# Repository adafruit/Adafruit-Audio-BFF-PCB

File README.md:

## Adafruit Audio BFF Add-on for QT Py and Xiao PCB

<a href="http://www.adafruit.com/products/5769"><br/>
Click here to purchase one from the Adafruit shop</a>

PCB files for the Adafruit Audio BFF Add-on for QT Py and Xiao. 

Format is EagleCAD schematic and board layout
* https://www.adafruit.com/product/5769

### Description

Our QT Py boards are a great way to make very small microcontroller projects that pack a ton of power - and now we have a way for you to turn many QT Py boards into powerful audio play projects that are super small!

This BFF comes with a MicroSD card slot that can address up to 64 GB of storage and a I2S 3 Watt amplifier, for high-quality audio playback, that can fit on the back of your miniature dev board. All together uses the SPI port plus 4 GPIO pins for card CS, and I2S data, clock and left-right select.

We call this the Adafruit Audio BFF - a "Best Friend Forever". When you were a kid, you may have learned about the "buddy" system; well, this product is kinda like that! A board that will watch your QT Py's back and give it more capabilities.

This PCB is designed to fit onto the back of any QT Py or Xiao board, it can be soldered into place or use pin and socket headers to make it removable. Onboard is a MAX98357 audio amplifier and picoblade-compatible connector for plugging in a 4 or 8 ohm speaker. We use A1 for the audio data, A2 for wordselect clock, and A3 for bitclock. The SD card connects over the SPI port: MOSI, MISO and SCK plus A0 for card select.

This pinout will work with ESP32 series, nRF52840, and RP2040 chipset boards. It won't work with the ATSAMD21 'original 'QT Py because those pins on the SAMD21 are not I2S capable. However, you could cut and rewire the traces to connect to the I2S pads if desired - personally, we recommend just upgrading to an RP2040 QT Py instead.

We include some header that you can solder to your QT Py. You can also pick up an Itsy Bitsy short female header kit to make it removable but compact, you'll just need to trim down the headers to 7 pins long.

* Comes as an assembled and tested PCB
* For any QT Py or Xiao boards
* Contains a MAX98357 3 Watt audio amplifier pre-configured for 'stereo' mix output and 9 dB gain which will work great for any project.
* Use any micro SD card that supports SPI mode with one CS pin.
* Connect to the speaker output with a picoblade-compatible 2-pin cable. We recommend this 3W 4 ohm speaker
* There are various Arduino / CircuitPython / MicroPython libraries can be used to talk to the SD card and I2S amplifier.

Speaker, microSD memory card, and QT Py are not included.

### License

Adafruit invests time and resources providing this open source design, please support Adafruit and open-source hardware by purchasing products from [Adafruit](https://www.adafruit.com)!

Designed by Limor Fried/Ladyada for Adafruit Industries.

Creative Commons Attribution/Share-Alike, all text above must be included in any redistribution. 
See license.txt for additional details.

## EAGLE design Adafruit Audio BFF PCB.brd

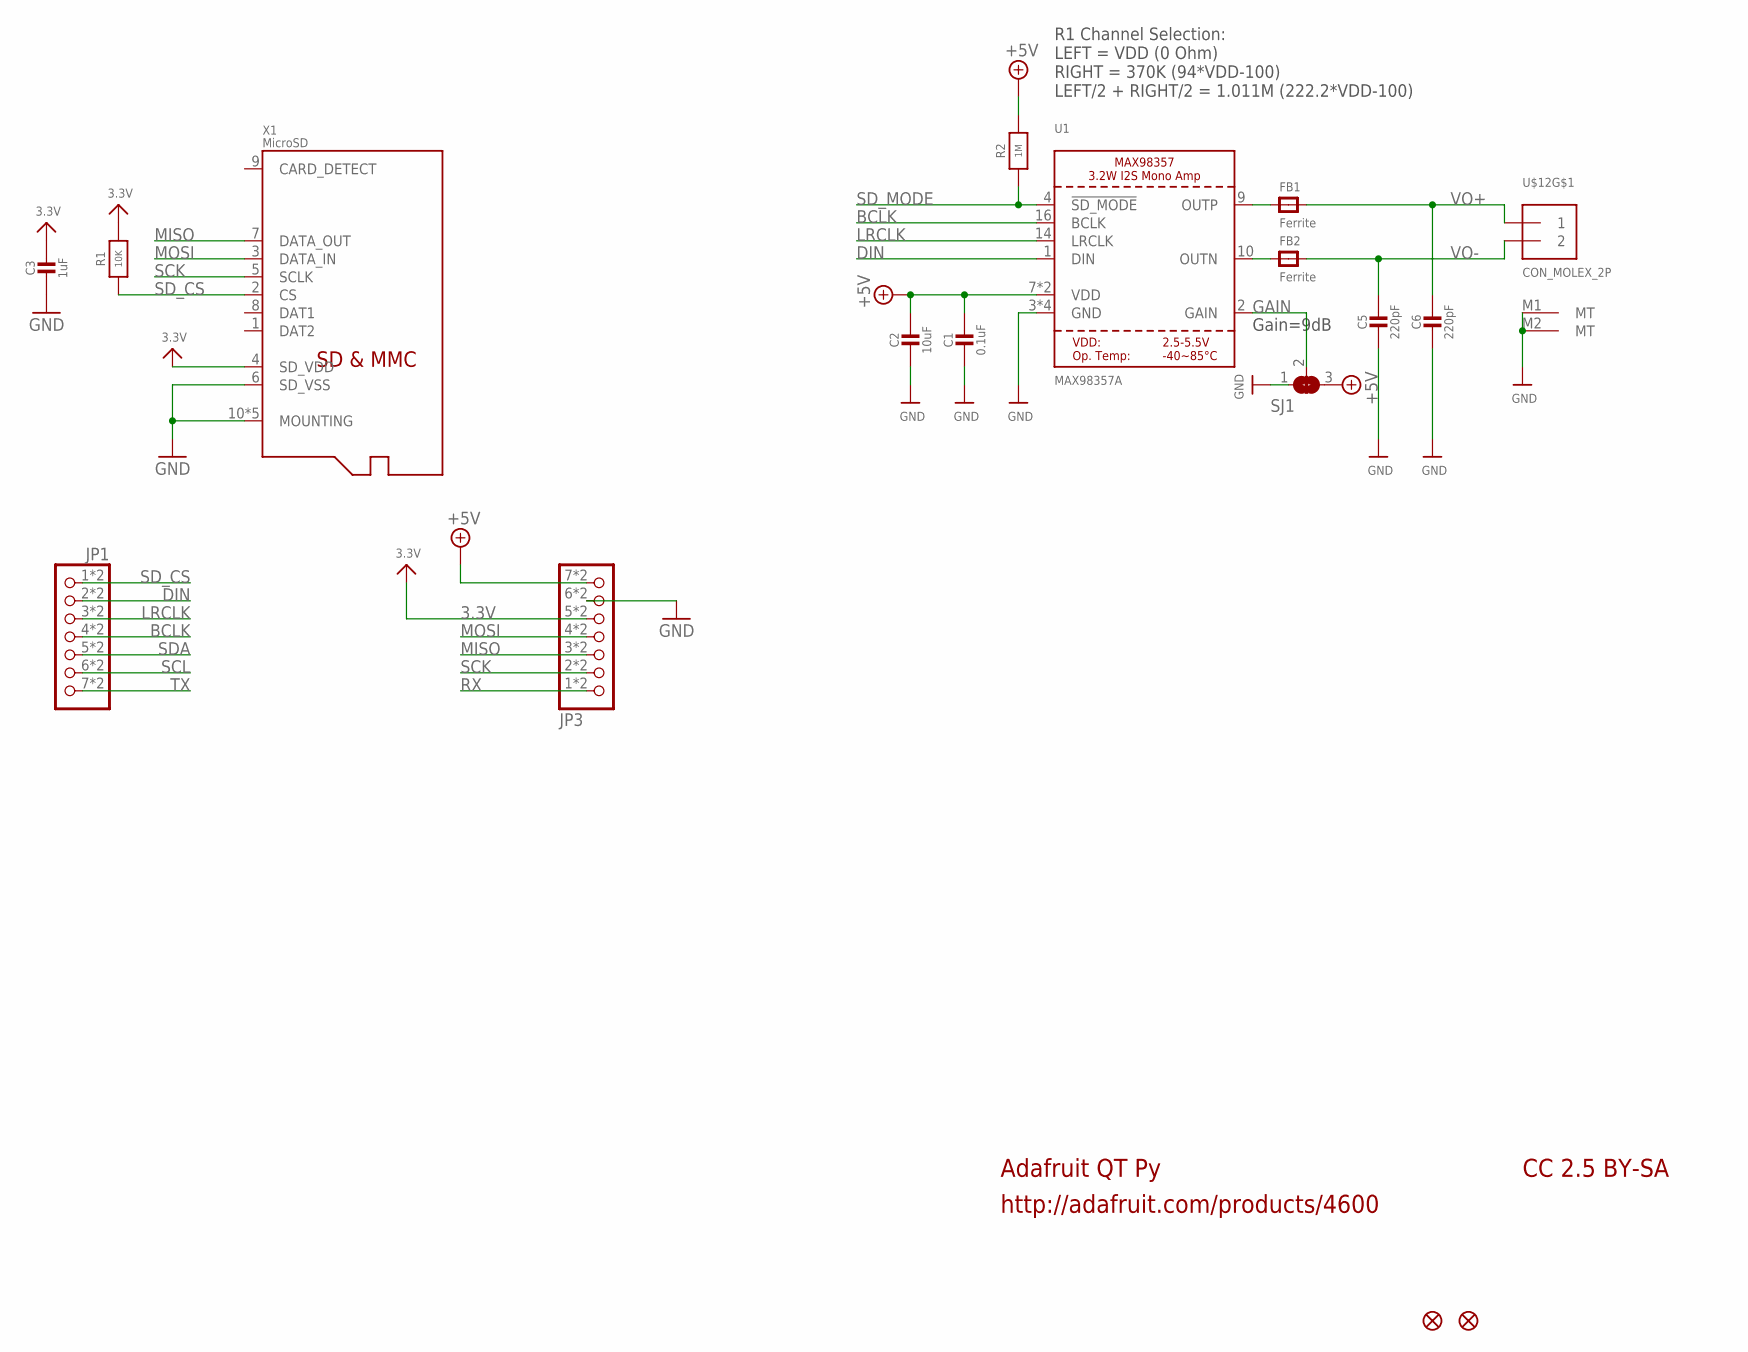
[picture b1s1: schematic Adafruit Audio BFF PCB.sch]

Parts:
C1: 0.1uF; _0402NO
C2: 10uF; 0805-NO
C3: 1uF; _0402NO
C5, C6: 220pF; _0402NO
FB1, FB2: Ferrite; _0402
JP1, JP3: HEADER-1X7_CASTEL; 1X07_CASTEL
R1: 10K; _0402NO
R2: 1M; _0402NO
SJ1: SOLDERJUMPER_2WAY; SOLDERJUMPER_2WAY_OPEN_NOPASTE
U1: MAX98357A; QFN16_3MM
U$6, U$8: FIDUCIAL_1MM
U$12: CON_MOLEX_2P; 53398-0271
X1: MicroSD; MOLEX_104031-0811

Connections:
3.3V: C3.1, JP3.5, JP3.5C (5), R1.2, X1.4 (SD_VDD)
+5V: C1.1, C2.1, JP3.7, JP3.7C (7), R2.2, SJ1.3, U1.7 (VDD), U1.8 (VDD)
BCLK: JP1.4, JP1.4C (4), U1.16 (BCLK)
DIN: JP1.2, JP1.2C (2), U1.1 (DIN)
GAIN: SJ1.2, U1.2 (GAIN)
GND: C1.2, C2.2, C3.2, C5.2, C6.2, JP3.6, JP3.6C (6), SJ1.1, U1.3 (GND), U1.11 (GND), U1.15 (GND), U1.THERMAL (GND), U$12.M1 (MT), U$12.M2 (MT), X1.6 (SD_VSS), X1.10 (MOUNTING), X1.G1 (MOUNTING), X1.G2 (MOUNTING), X1.G3 (MOUNTING), X1.G4 (MOUNTING)
LRCLK: JP1.3, JP1.3C (3), U1.14 (LRCLK)
MISO: JP3.3, JP3.3C (3), X1.7 (DATA_OUT)
MOSI: JP3.4, JP3.4C (4), X1.3 (DATA_IN)
unnamed: FB2.1, U1.10 (OUTN)
unnamed: FB1.1, U1.9 (OUTP)
RX: JP3.1, JP3.1C (1)
SCK: JP3.2, JP3.2C (2), X1.5 (SCLK)
SCL: JP1.6, JP1.6C (6)
SDA: JP1.5, JP1.5C (5)
SD_CS: JP1.1, JP1.1C (1), R1.1, X1.2 (CS)
SD_MODE: R2.1, U1.4 (!SD_MODE)
TX: JP1.7, JP1.7C (7)
VO+: C6.1, FB1.2, U$12.1
VO-: C5.1, FB2.2, U$12.2

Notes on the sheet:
Adafruit QT Py
http://adafruit.com/products/4600
CC 2.5 BY-SA
R1 Channel Selection: LEFT = VDD (0 Ohm) RIGHT = 370K (94*VDD-100) LEFT/2 + RIGHT/2 = 1.011M (222.2*VDD-100)
Gain=9dB

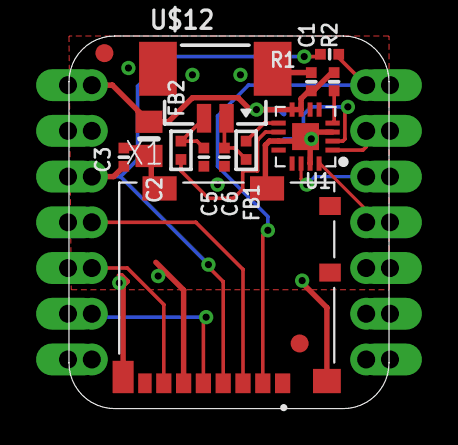
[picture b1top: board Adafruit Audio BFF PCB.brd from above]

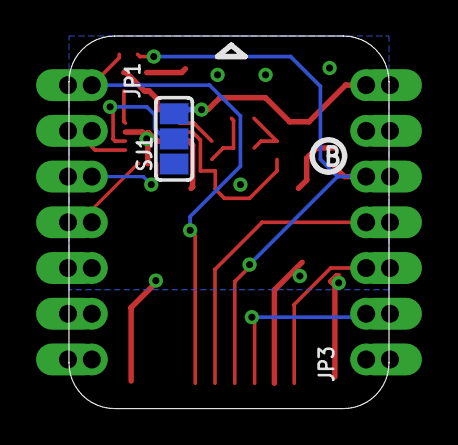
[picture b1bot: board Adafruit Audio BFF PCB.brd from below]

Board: 2 copper layers, 17.8 x 20.7 mm, 30 parts (11 on the bottom side), 20 nets.

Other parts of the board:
PLABEL6: PLABEL6
PLABEL7: PLABEL7
PLABEL8: PLABEL8
PLABEL9: PLABEL9
PLABEL10: PLABEL10
PLABEL11: PLABEL11
PLABEL12: PLABEL12
PLABEL13: PLABEL13
PLABEL14: PLABEL14
PLABEL15: PLABEL15
PLABEL16: PLABEL16
PLABEL17: PLABEL17
U$3: PCBFEAT-REV-040

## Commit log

2023-07-17 adding cookiecutter output

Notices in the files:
parts and their libraries:
microbuilder: This work is placed in the public domain, and may be freely used for commercial and non-commercial work with the following conditions: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
